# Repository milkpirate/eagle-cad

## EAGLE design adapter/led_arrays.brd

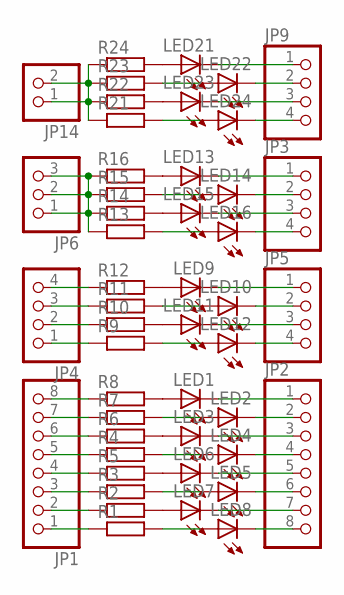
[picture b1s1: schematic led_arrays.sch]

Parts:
JP1, JP2: PINHD-1X8; 1X08
JP3, JP4, JP5, JP9: PINHD-1X4; 1X04
JP6: PINHD-1X3; 1X03
JP14: PINHD-1X2; 1X02
LED1, LED2, LED3, LED4, LED5, LED6, LED7, LED8, LED9, LED10, LED11, LED12, LED13, LED14, LED15, LED16, LED21, LED22, LED23, LED24: LEDSML0805; SML0805
R1, R2, R3, R4, R5, R6, R7, R8, R9, R10, R11, R12, R13, R14, R15, R16, R21, R22, R23, R24: R-EU_M0805; M0805

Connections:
unnamed: JP1.8, R8.1
unnamed: JP1.7, R7.1
unnamed: JP1.6, R6.1
unnamed: JP1.4, R5.1
unnamed: JP1.5, R4.1
unnamed: JP1.3, R3.1
unnamed: JP1.2, R2.1
unnamed: JP1.1, R1.1
unnamed: LED1.A, R8.2
unnamed: LED2.A, R7.2
unnamed: LED3.A, R6.2
unnamed: LED4.A, R4.2
unnamed: LED6.A, R5.2
unnamed: LED5.A, R3.2
unnamed: LED7.A, R2.2
unnamed: LED8.A, R1.2
unnamed: JP2.2, LED2.C
unnamed: JP2.4, LED4.C
unnamed: JP2.6, LED5.C
unnamed: JP2.8, LED8.C
unnamed: JP2.1, LED1.C
unnamed: JP2.3, LED3.C
unnamed: JP2.5, LED6.C
unnamed: JP2.7, LED7.C
unnamed: LED9.A, R12.2
unnamed: LED10.A, R11.2
unnamed: LED11.A, R10.2
unnamed: LED12.A, R9.2
unnamed: JP5.1, LED9.C
unnamed: JP5.3, LED11.C
unnamed: LED13.A, R16.2
unnamed: LED15.A, R14.2
unnamed: JP3.2, LED14.C
unnamed: JP3.4, LED16.C
unnamed: JP4.1, R9.1
unnamed: JP4.2, R10.1
unnamed: JP4.3, R11.1
unnamed: JP4.4, R12.1
unnamed: JP6.1, JP6.2, JP6.3, R13.1, R14.1, R15.1, R16.1
unnamed: LED14.A, R15.2
unnamed: JP5.2, LED10.C
unnamed: JP5.4, LED12.C
unnamed: JP3.3, LED15.C
unnamed: JP3.1, LED13.C
unnamed: LED16.A, R13.2
unnamed: LED21.A, R24.2
unnamed: LED23.A, R22.2
unnamed: JP9.2, LED22.C
unnamed: JP9.4, LED24.C
unnamed: JP14.1, JP14.2, R21.1, R22.1, R23.1, R24.1
unnamed: LED22.A, R23.2
unnamed: JP9.3, LED23.C
unnamed: JP9.1, LED21.C
unnamed: LED24.A, R21.2

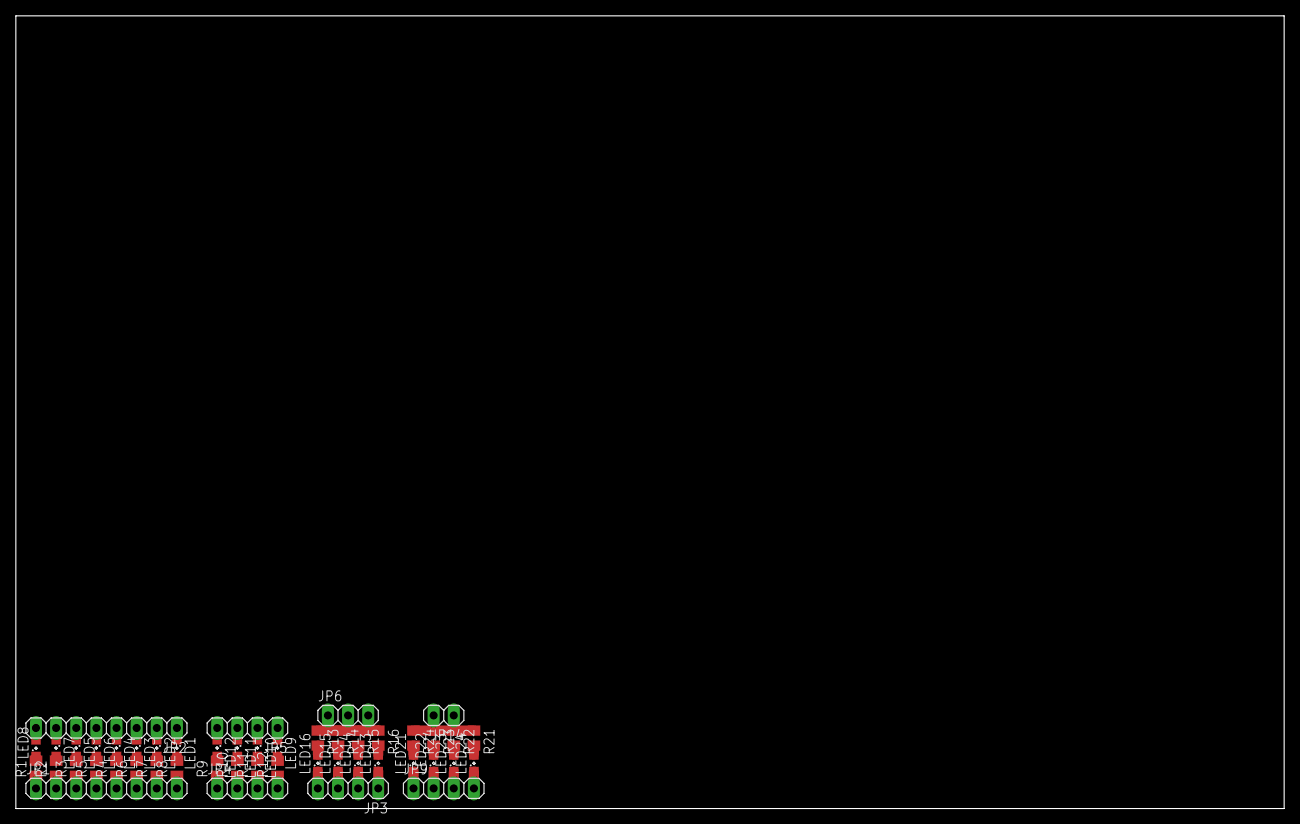
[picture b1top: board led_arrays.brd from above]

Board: 2 copper layers, 160.0 x 100.0 mm, 48 parts (0 on the bottom side), 54 nets.

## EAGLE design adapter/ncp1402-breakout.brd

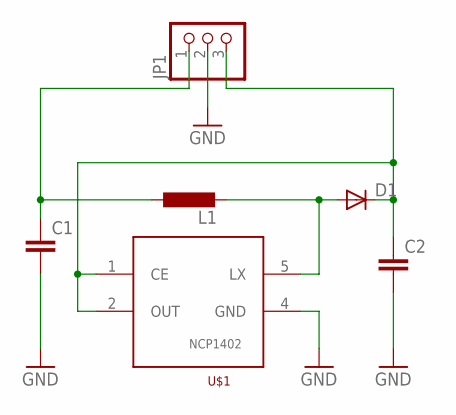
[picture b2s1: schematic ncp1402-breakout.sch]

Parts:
C1, C2: C-EUC1210; C1210
D1: DIODE-SOD80C; SOD80C
JP1: PINHD-1X3; 1X03
L1: L-EUL1812; L1812
U$1: NCP1402-SOT23-5; SOT23-5

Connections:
GND: C1.2, C2.2, JP1.2, U$1.4 (GND)
unnamed: C2.1, D1.C, JP1.3, U$1.1 (CE), U$1.2 (OUT)
unnamed: D1.A, L1.2, U$1.5 (LX)
unnamed: C1.1, JP1.1, L1.1

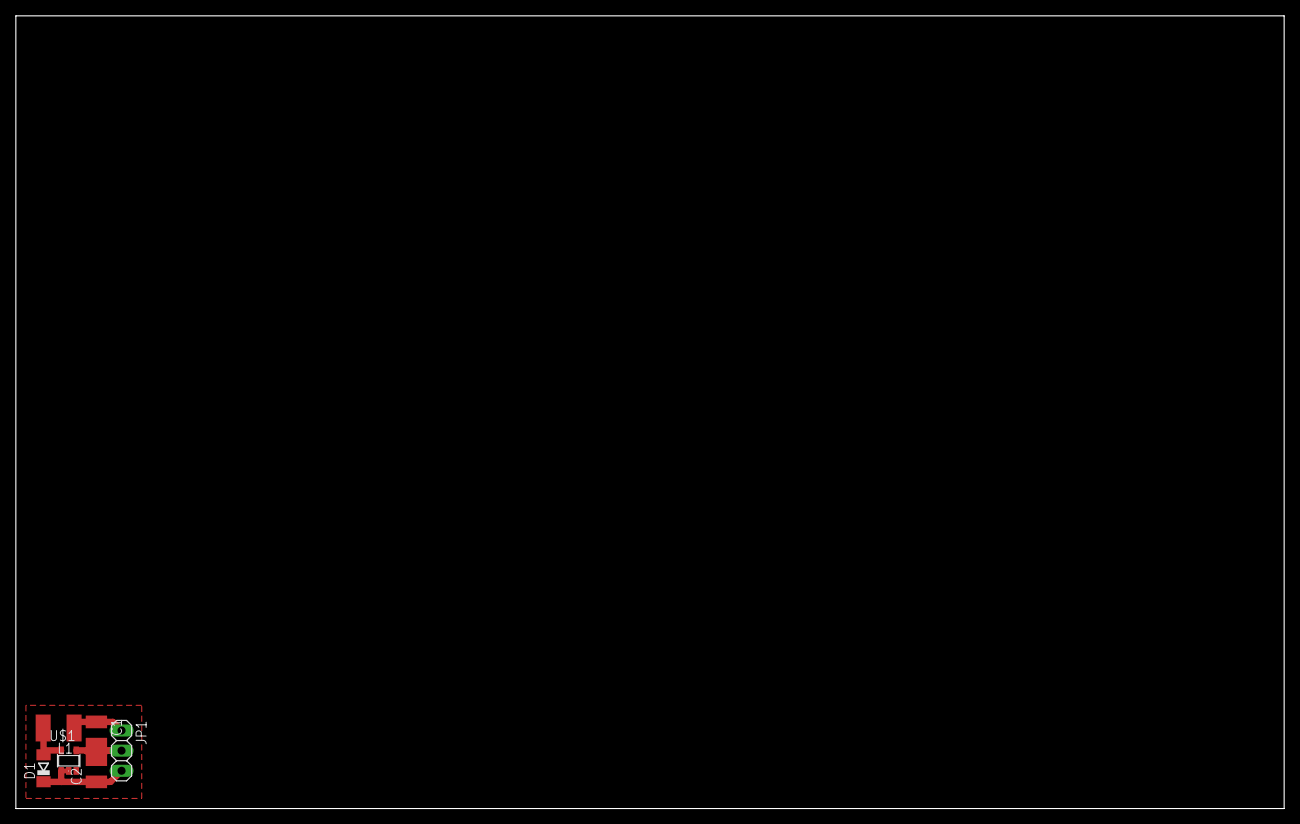
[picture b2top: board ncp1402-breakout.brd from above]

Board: 2 copper layers, 160.0 x 100.0 mm, 6 parts (0 on the bottom side), 4 nets.

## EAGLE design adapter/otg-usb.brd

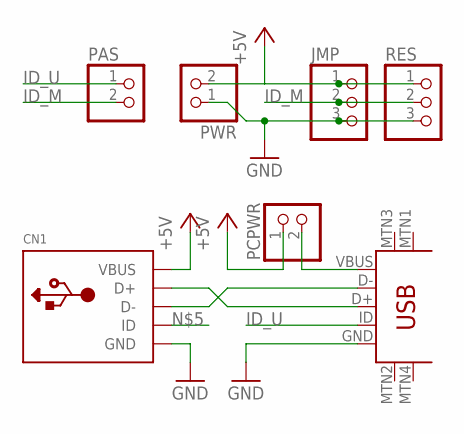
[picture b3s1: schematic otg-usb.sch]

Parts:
CN1: USBMINIB; USB-MINIB
JMP: PINHD-1X3; 1X03
PAS: PINHD-1X2; 1X02
PCPWR: PINHD-1X2; 1X02
PWR: PINHD-1X2; 1X02
RES: PINHD-1X3; 1X03
U$1: USB-MINIB-5PIN; USB-MINIB

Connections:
+5V: CN1.VBUS, PCPWR.1, PWR.2
GND: CN1.GND, JMP.3, PWR.1, RES.3, U$1.GND
ID_M: JMP.2, PAS.2, RES.2
ID_U: PAS.1, U$1.ID
unnamed: CN1.D+, U$1.D+
unnamed: CN1.D-, U$1.D-
unnamed: JMP.1, RES.1
unnamed: PCPWR.2, U$1.VBUS

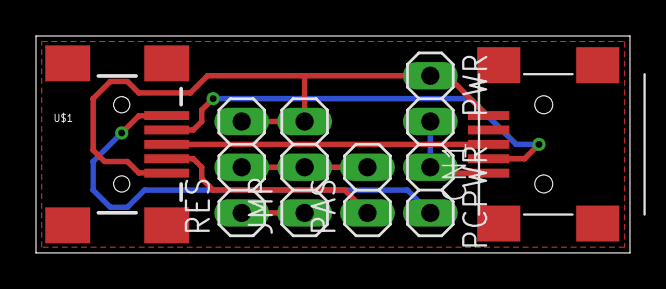
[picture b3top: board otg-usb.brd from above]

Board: 2 copper layers, 33.0 x 12.1 mm, 7 parts (0 on the bottom side), 8 nets.

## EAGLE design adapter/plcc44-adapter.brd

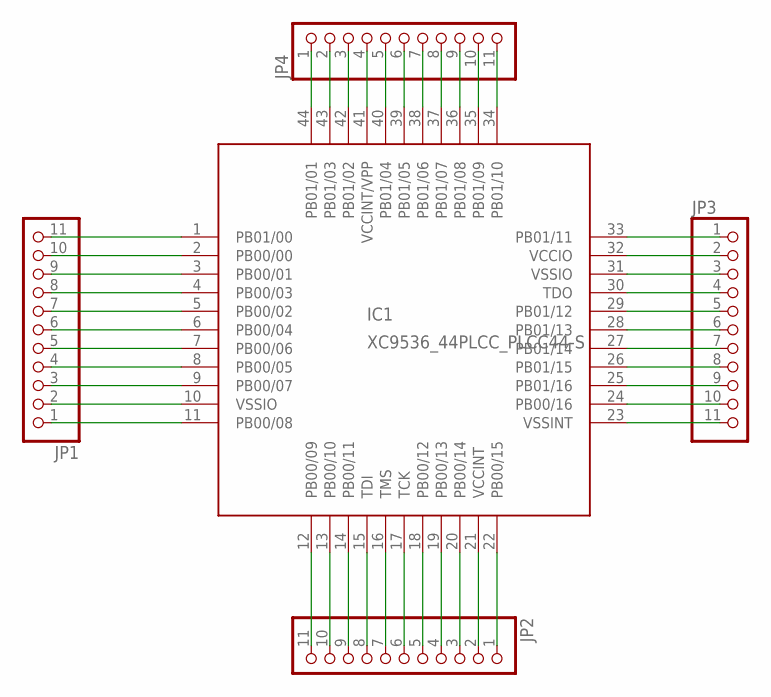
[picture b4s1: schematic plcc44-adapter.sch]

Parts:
IC1: XC9536_44PLCC_PLCC44-S; PLCC-S44
JP1, JP2, JP3, JP4: PINHD-1X11; 1X11

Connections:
unnamed: IC1.11 (PB00/08), JP1.1
unnamed: IC1.10 (VSSIO), JP1.2
unnamed: IC1.9 (PB00/07), JP1.3
unnamed: IC1.8 (PB00/05), JP1.4
unnamed: IC1.7 (PB00/06), JP1.5
unnamed: IC1.6 (PB00/04), JP1.6
unnamed: IC1.5 (PB00/02), JP1.7
unnamed: IC1.4 (PB00/03), JP1.8
unnamed: IC1.3 (PB00/01), JP1.9
unnamed: IC1.2 (PB00/00), JP1.10
unnamed: IC1.1 (PB01/00), JP1.11
unnamed: IC1.22 (PB00/15), JP2.1
unnamed: IC1.21 (VCCINT), JP2.2
unnamed: IC1.20 (PB00/14), JP2.3
unnamed: IC1.19 (PB00/13), JP2.4
unnamed: IC1.18 (PB00/12), JP2.5
unnamed: IC1.17 (TCK), JP2.6
unnamed: IC1.16 (TMS), JP2.7
unnamed: IC1.15 (TDI), JP2.8
unnamed: IC1.14 (PB00/11), JP2.9
unnamed: IC1.13 (PB00/10), JP2.10
unnamed: IC1.12 (PB00/09), JP2.11
unnamed: IC1.33 (PB01/11), JP3.1
unnamed: IC1.32 (VCCIO), JP3.2
unnamed: IC1.31 (VSSIO), JP3.3
unnamed: IC1.30 (TDO), JP3.4
unnamed: IC1.29 (PB01/12), JP3.5
unnamed: IC1.28 (PB01/13), JP3.6
unnamed: IC1.27 (PB01/14), JP3.7
unnamed: IC1.26 (PB01/15), JP3.8
unnamed: IC1.25 (PB01/16), JP3.9
unnamed: IC1.24 (PB00/16), JP3.10
unnamed: IC1.23 (VSSINT), JP3.11
unnamed: IC1.44 (PB01/01), JP4.1
unnamed: IC1.43 (PB01/03), JP4.2
unnamed: IC1.42 (PB01/02), JP4.3
unnamed: IC1.41 (VCCINT/VPP), JP4.4
unnamed: IC1.40 (PB01/04), JP4.5
unnamed: IC1.39 (PB01/05), JP4.6
unnamed: IC1.38 (PB01/06), JP4.7
unnamed: IC1.37 (PB01/07), JP4.8
unnamed: IC1.36 (PB01/08), JP4.9
unnamed: IC1.35 (PB01/09), JP4.10
unnamed: IC1.34 (PB01/10), JP4.11

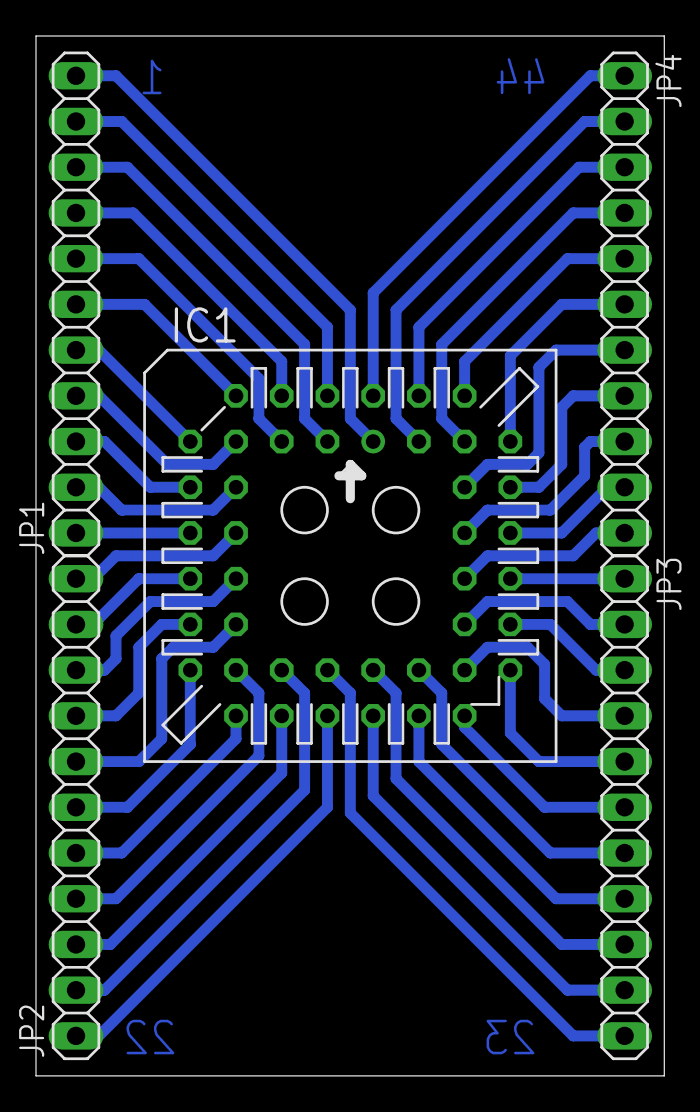
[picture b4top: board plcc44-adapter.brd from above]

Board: 2 copper layers, 34.9 x 57.8 mm, 5 parts (0 on the bottom side), 44 nets.

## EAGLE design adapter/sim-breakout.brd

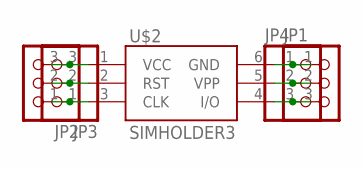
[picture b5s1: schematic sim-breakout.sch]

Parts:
JP1, JP2, JP3, JP4: PINHD-1X3; 1X03
U$2: SIMHOLDER3

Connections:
unnamed: JP1.1, JP4.1, U$2.6 (GND)
unnamed: JP1.2, JP4.2, U$2.5 (VPP)
unnamed: JP1.3, JP4.3, U$2.4 (I/O)
unnamed: JP2.1, JP3.1, U$2.3 (CLK)
unnamed: JP2.2, JP3.2, U$2.2 (RST)
unnamed: JP2.3, JP3.3, U$2.1 (VCC)

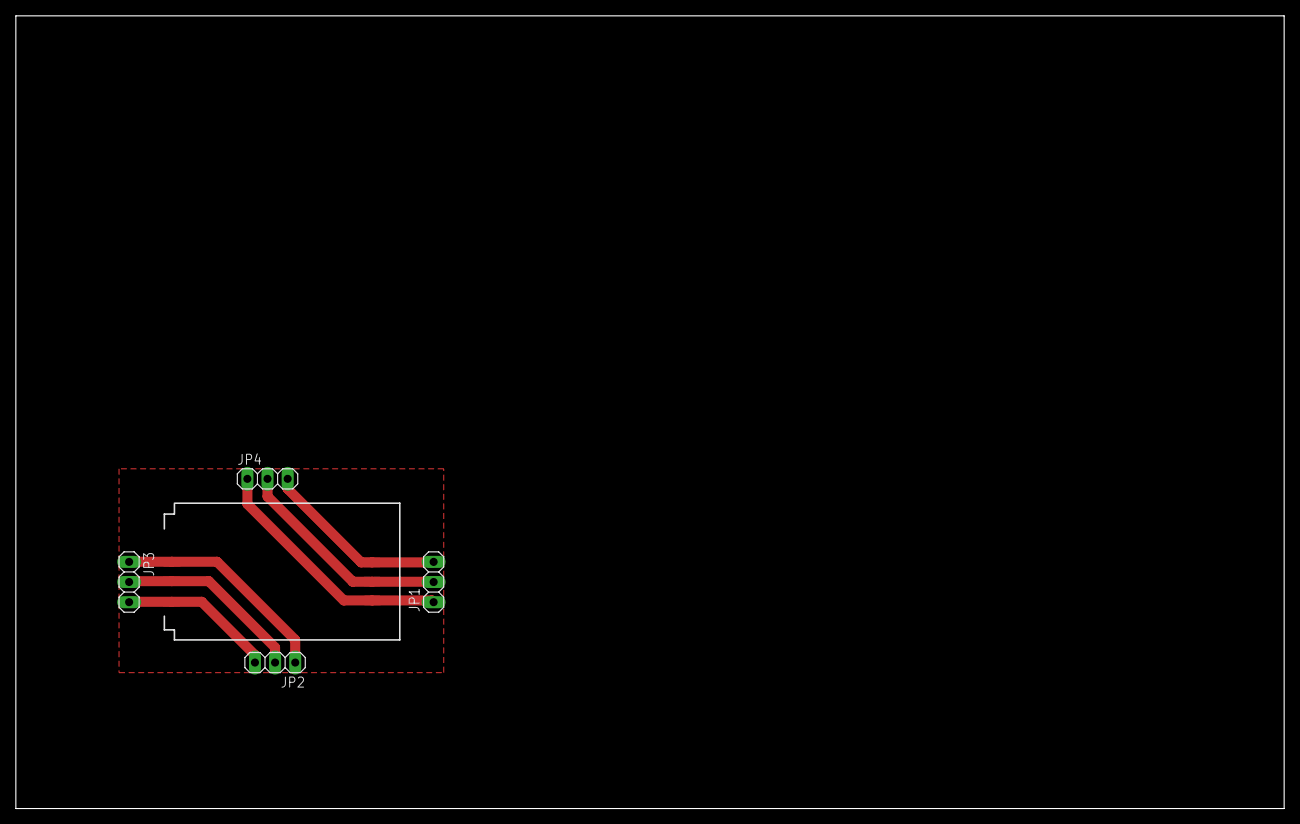
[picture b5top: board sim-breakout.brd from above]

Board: 2 copper layers, 160.0 x 100.0 mm, 5 parts (0 on the bottom side), 6 nets.

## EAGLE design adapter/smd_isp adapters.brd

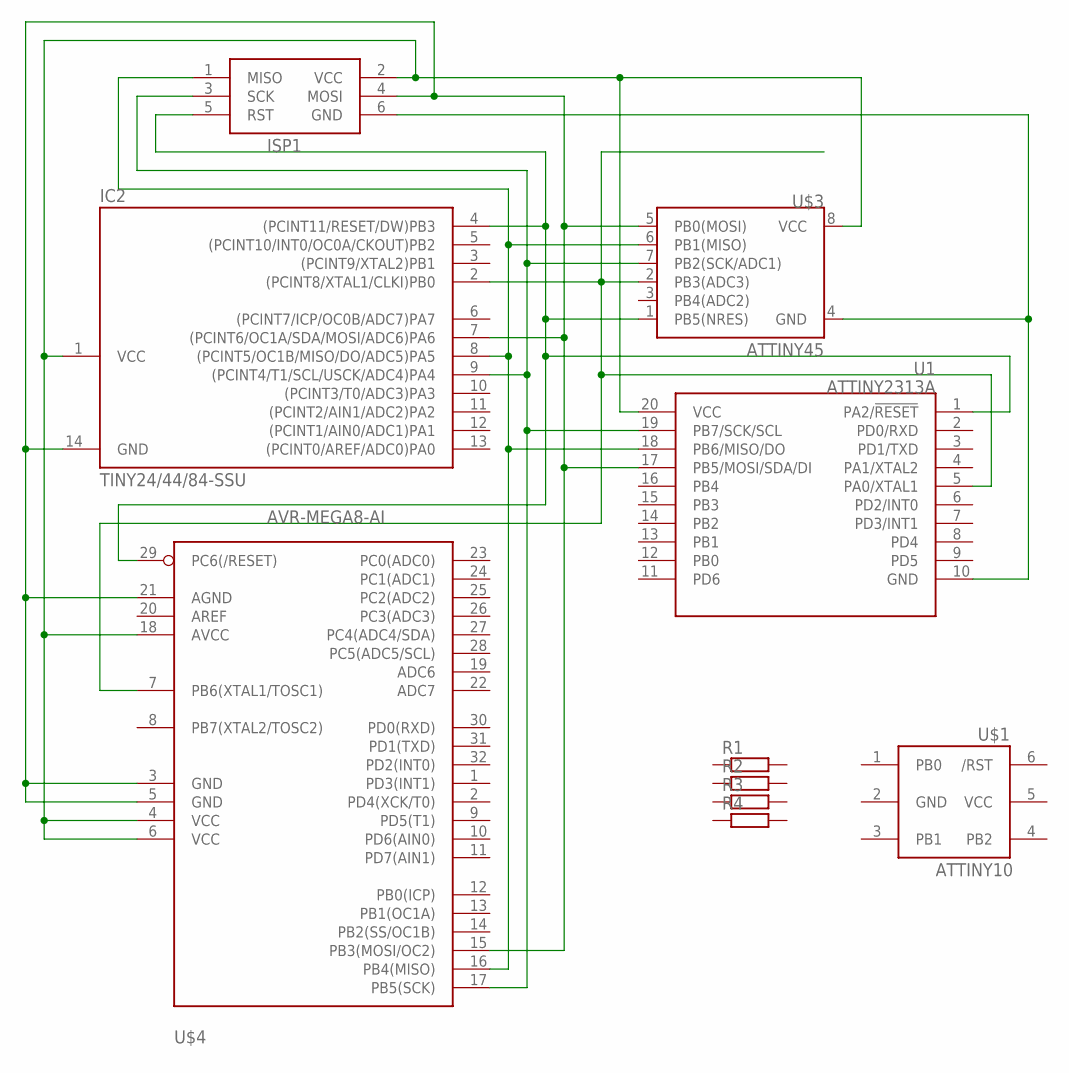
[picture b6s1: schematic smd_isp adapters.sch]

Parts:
IC2: TINY24/44/84-SSU; SOIC14
ISP1: AVRISP-6; AVRISP
R1, R2, R3, R4: R-EU_R0805; R0805
U1: ATTINY2313A; SOP20W
U$1: ATTINY10; SOT23-6
U$3: ATTINY45; SO08-EIAJ
U$4: AVR-MEGA8-AI; TQFP32-08

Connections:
GND: U$1.2 (GND)
MISO: IC2.8 ((PCINT5/OC1B/MISO/DO/ADC5)PA5), ISP1.1 (MISO), U1.18 (PB6/MISO/DO), U$3.6 (PB1(MISO)), U$4.16 (PB4(MISO))
MOSI: IC2.7 ((PCINT6/OC1A/SDA/MOSI/ADC6)PA6), IC2.14 (GND), ISP1.4 (MOSI), U1.17 (PB5/MOSI/SDA/DI), U$3.5 (PB0(MOSI)), U$4.3 (GND), U$4.5 (GND), U$4.15 (PB3(MOSI/OC2)), U$4.21 (AGND)
unnamed: IC2.2 ((PCINT8/XTAL1/CLKI)PB0), U1.5 (PA0/XTAL1), U$3.2 (PB3(ADC3)), U$4.7 (PB6(XTAL1/TOSC1))
unnamed: ISP1.6 (GND), U1.10 (GND), U$3.4 (GND)
unnamed: IC2.1 (VCC), ISP1.2 (VCC), U1.20 (VCC), U$3.8 (VCC), U$4.4 (VCC), U$4.6 (VCC), U$4.18 (AVCC)
RST: IC2.4 ((PCINT11/RESET/DW)PB3), ISP1.5 (RST), U1.1 (PA2/!RESET), U$3.1 (PB5(NRES)), U$4.29 (PC6(/RESET))
SCK: IC2.9 ((PCINT4/T1/SCL/USCK/ADC4)PA4), ISP1.3 (SCK), U1.19 (PB7/SCK/SCL), U$3.7 (PB2(SCK/ADC1)), U$4.17 (PB5(SCK))
VCC: U$1.5 (VCC)

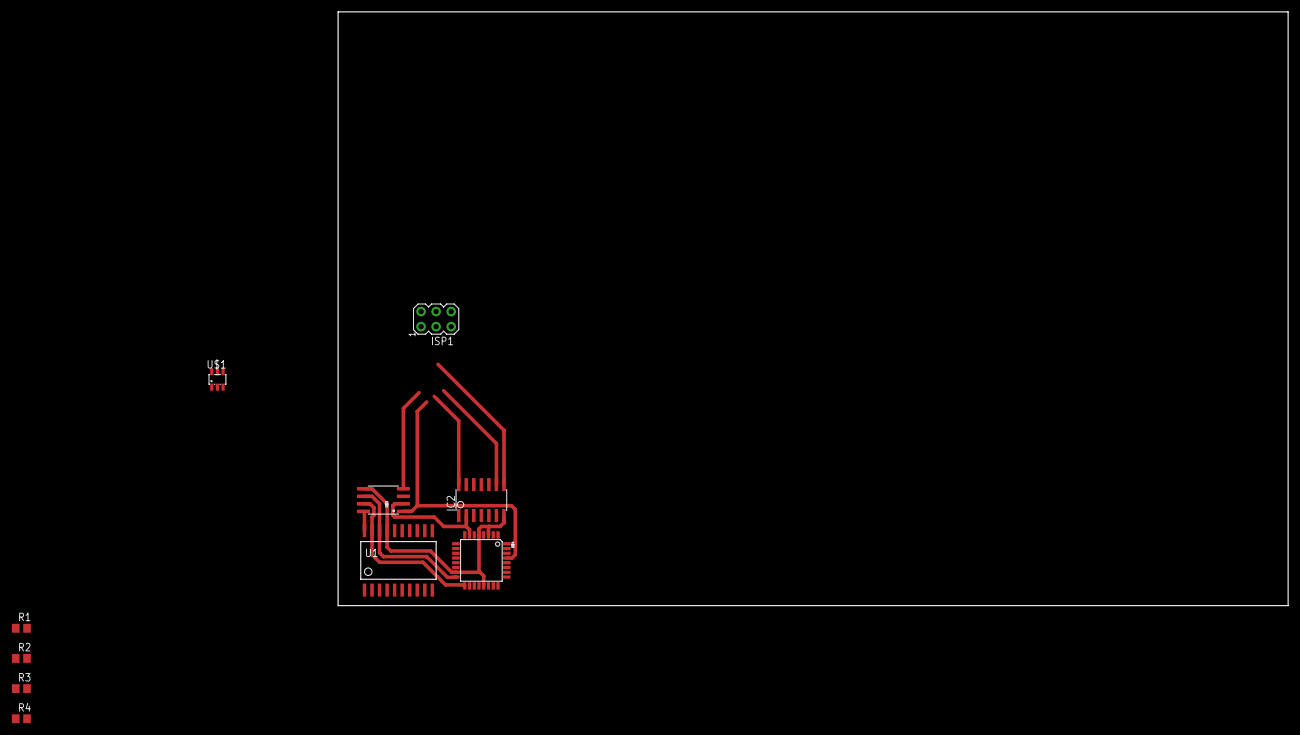
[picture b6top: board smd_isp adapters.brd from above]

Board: 2 copper layers, 160.0 x 100.0 mm, 10 parts (0 on the bottom side), 7 nets.

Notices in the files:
parts and their libraries:
SparkFun-Connectors: Licensing: Creative Commons ShareAlike 4.0 International - https://creativecommons.org/licenses/by-sa/4.0
SparkFun-Connectors: Licensing: CC v3.0 Share-Alike You are welcome to use this library for commercial purposes.
